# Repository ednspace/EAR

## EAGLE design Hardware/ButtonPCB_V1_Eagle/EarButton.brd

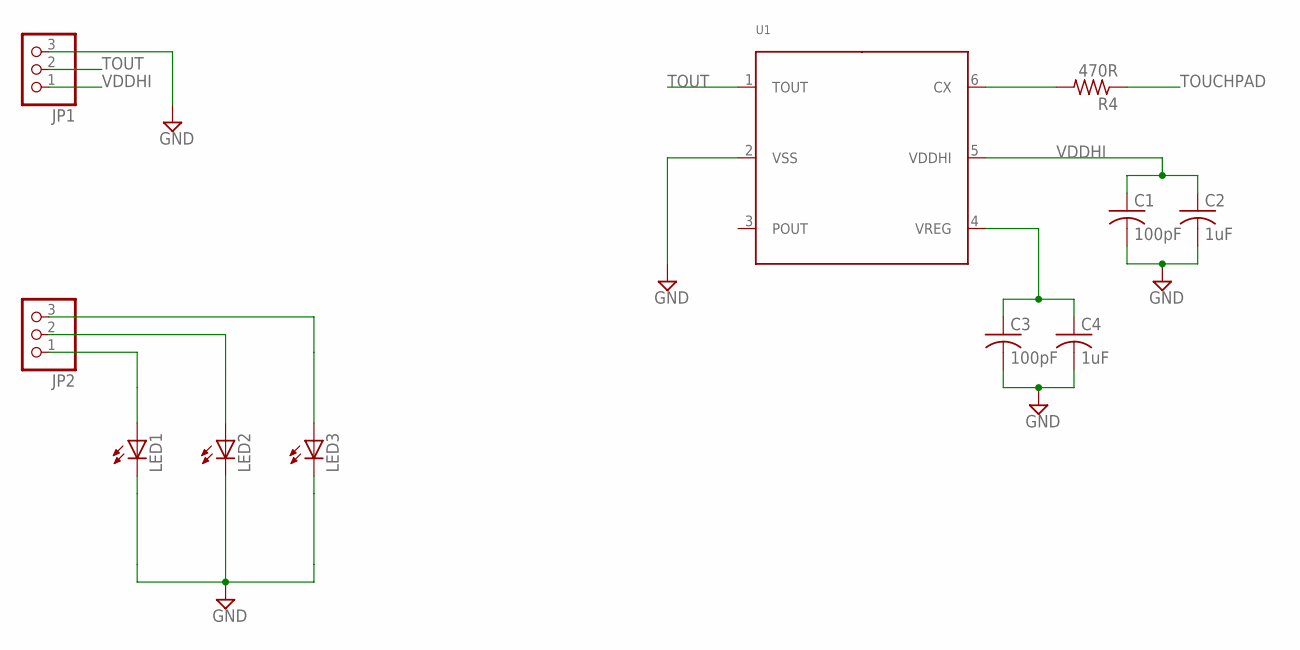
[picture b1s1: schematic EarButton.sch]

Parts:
C1, C3: 100pF; C0603K
C2, C4: 1uF; C0603K
JP1, JP2: PINHD-1X3; 1X03
LED1, LED2, LED3: LEDCHIPLED_1206; CHIPLED_1206
R4: 470R; R0603
U1: IQS127; SOT23-6

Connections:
GND: C1.2, C2.2, C3.2, C4.2, JP1.3, LED1.C, LED2.C, LED3.C, U1.2 (VSS)
unnamed: C3.1, C4.1, U1.4 (VREG)
unnamed: JP2.1, LED1.A
unnamed: JP2.2, LED2.A
unnamed: JP2.3, LED3.A
unnamed: R4.2, U1.6 (CX)
TOUCHPAD: R4.1
TOUT: JP1.2, U1.1 (TOUT)
VDDHI: C1.1, C2.1, JP1.1, U1.5 (VDDHI)

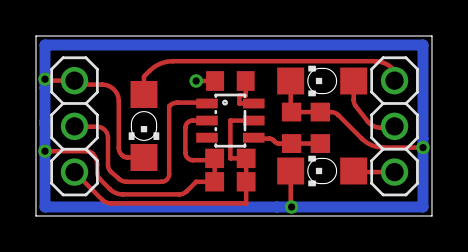
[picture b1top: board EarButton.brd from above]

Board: 2 copper layers, 22.0 x 10.0 mm, 11 parts (0 on the bottom side), 8 nets.

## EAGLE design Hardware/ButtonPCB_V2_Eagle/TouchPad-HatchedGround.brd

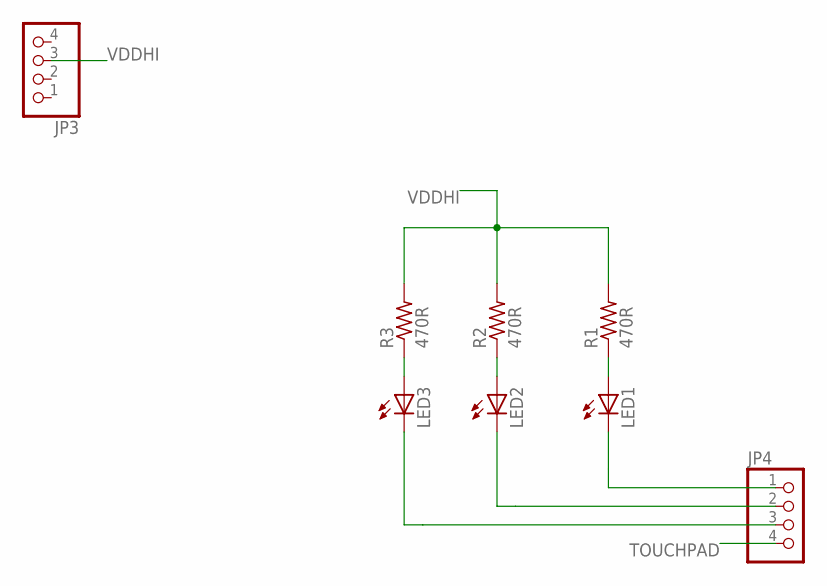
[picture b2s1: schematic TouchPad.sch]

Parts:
JP3, JP4: PINHD-1X4; 1X04
LED1, LED2, LED3: LEDCHIPLED_1206; CHIPLED_1206
R1, R2, R3: 470R; R0603

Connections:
GND: JP3.4
unnamed: LED1.A, R1.1
unnamed: LED2.A, R2.1
unnamed: LED3.A, R3.1
unnamed: JP4.1, LED1.C
unnamed: JP4.2, LED2.C
unnamed: JP4.3, LED3.C
TOUCHPAD: JP4.4
VDDHI: JP3.3, R1.2, R2.2, R3.2

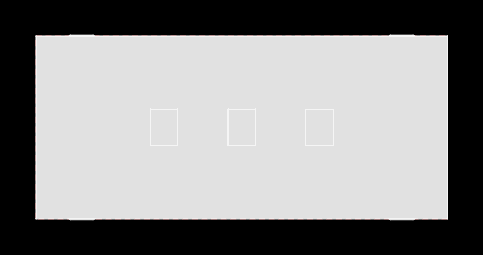
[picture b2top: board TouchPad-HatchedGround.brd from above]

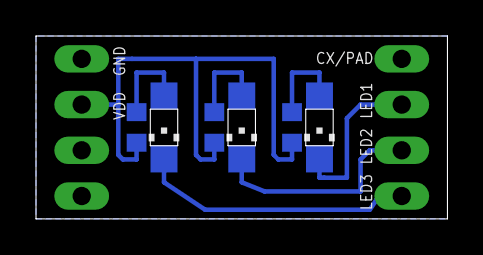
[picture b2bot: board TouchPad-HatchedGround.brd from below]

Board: 2 copper layers, 22.9 x 10.2 mm, 8 parts (6 on the bottom side), 7 nets.

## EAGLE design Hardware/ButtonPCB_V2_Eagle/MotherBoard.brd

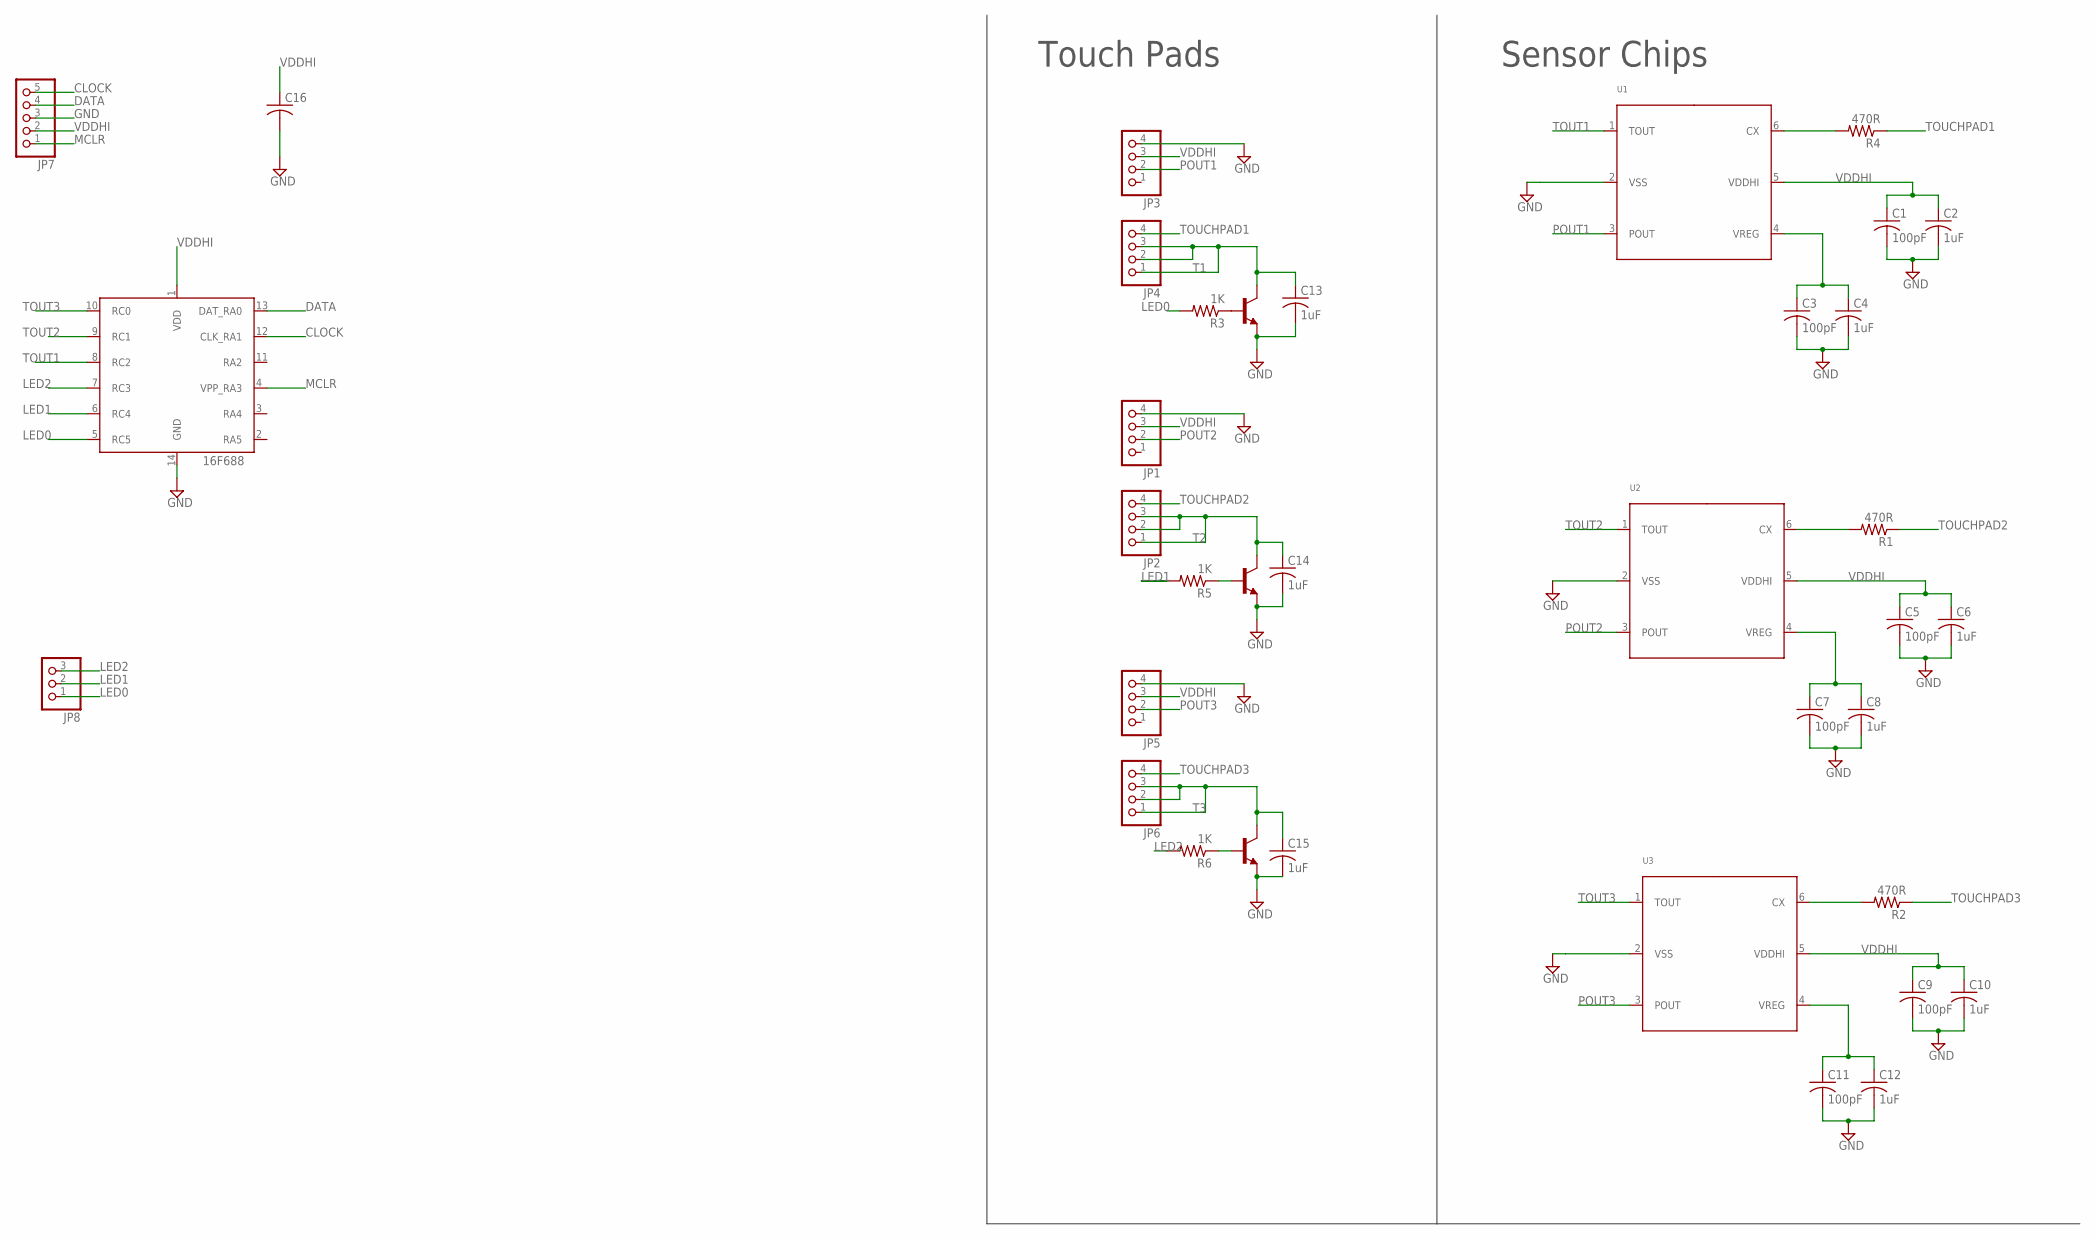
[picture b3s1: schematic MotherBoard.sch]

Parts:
C1, C3, C5, C7, C9, C11: 100pF; C0603K
C2, C4, C6, C8, C10, C12, C13, C14, C15: 1uF; C0603K
C16: C-USC1206; C1206
JP1, JP2, JP3, JP4, JP5, JP6: PINHD-1X4; 1X04
JP7: PINHD-1X5; 1X05
JP8: PINHD-1X3; 1X03
R1, R2, R4: 470R; R0603
R3, R5, R6: 1K; R0603
T1, T2, T3: BC818-NPN-SOT23-BEC; SOT23-BEC
U1, U2, U3: IQS127; SOT23-6
U$1: PIC16F688SOIC14; SOIC14

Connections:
CLOCK: JP7.5, U$1.12 (CLK_RA1)
DATA: JP7.4, U$1.13 (DAT_RA0)
GND: C1.2, C2.2, C3.2, C4.2, C5.2, C6.2, C7.2, C8.2, C9.2, C10.2, C11.2, C12.2, C13.2, C14.2, C15.2, C16.2, JP1.4, JP3.4, JP5.4, JP7.3, T1.E, T2.E, T3.E, U1.2 (VSS), U2.2 (VSS), U3.2 (VSS), U$1.14 (GND)
LED0: JP8.1, R3.2, U$1.5 (RC5)
LED1: JP8.2, R5.2, U$1.6 (RC4)
LED2: JP8.3, R6.2, U$1.7 (RC3)
MCLR: JP7.1, U$1.4 (VPP_RA3)
unnamed: C7.1, C8.1, U2.4 (VREG)
unnamed: R1.2, U2.6 (CX)
unnamed: C3.1, C4.1, U1.4 (VREG)
unnamed: C13.1, JP4.1, JP4.2, JP4.3, T1.C
unnamed: C14.1, JP2.1, JP2.2, JP2.3, T2.C
unnamed: C15.1, JP6.1, JP6.2, JP6.3, T3.C
unnamed: C11.1, C12.1, U3.4 (VREG)
unnamed: R4.2, U1.6 (CX)
unnamed: R3.1, T1.B
unnamed: R5.1, T2.B
unnamed: R6.1, T3.B
unnamed: R2.2, U3.6 (CX)
POUT1: JP3.2, U1.3 (POUT)
POUT2: JP1.2, U2.3 (POUT)
POUT3: JP5.2, U3.3 (POUT)
TOUCHPAD1: JP4.4, R4.1
TOUCHPAD2: JP2.4, R1.1
TOUCHPAD3: JP6.4, R2.1
TOUT1: U1.1 (TOUT), U$1.8 (RC2)
TOUT2: U2.1 (TOUT), U$1.9 (RC1)
TOUT3: U3.1 (TOUT), U$1.10 (RC0)
VDDHI: C1.1, C2.1, C5.1, C6.1, C9.1, C10.1, C16.1, JP1.3, JP3.3, JP5.3, JP7.2, U1.5 (VDDHI), U2.5 (VDDHI), U3.5 (VDDHI), U$1.1 (VDD)

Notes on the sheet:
Touch Pads
Sensor Chips

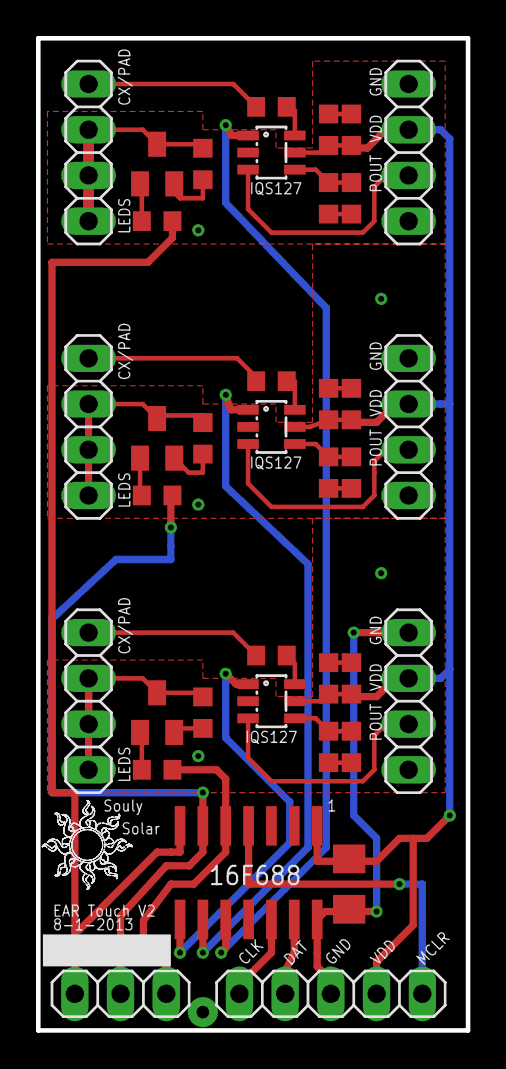
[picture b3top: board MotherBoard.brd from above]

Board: 2 copper layers, 23.9 x 55.1 mm, 38 parts (0 on the bottom side), 29 nets.

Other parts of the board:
U$2: SOULY-LOGO

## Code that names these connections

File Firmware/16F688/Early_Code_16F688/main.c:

#include <16F688.h>
//#device adc=10
#use delay(clock=8000000)
#fuses NOWDT,INTRC_IO, NOPROTECT, BROWNOUT, NOMCLR, NOCPD, PUT, NOIESO, NOFCMEN
//#use rs232(baud=9600,parity=N,xmit=PIN_C4,rcv=PIN_C5,bits=9)

#define LED0 PIN_C5
#define LED1 PIN_C4
#define LED2 PIN_C3

#define button0 PIN_C2
#define button1 PIN_C1
#define button2 PIN_C0

int1 state0,state1,state2;


void main(){
   setup_oscillator( OSC_8MHZ );
   //setup_adc_ports(sAN6|VSS_VDD);
   setup_adc(ADC_CLOCK_INTERNAL);
   //setup_counters(RTCC_INTERNAL,RTCC_DIV_1);
   //setup_timer_1(T1_DISABLED);
   setup_comparator(NC_NC_NC_NC);
   setup_vref(FALSE);

state0 = read_eeprom (0);
state1 = read_eeprom (1);
state2 = read_eeprom (2);

//Test the LEDs
/*
while (1){
output_low(LED0);
output_low(LED1);
output_low(LED2);
delay_ms(1000);
output_high(LED0);
output_high(LED1);
output_high(LED2);
delay_ms(1000);
}
*/

//The LEDs are an active High because of the NPN transistor driving the low side
if (state0 == 1)
output_high(LED0);

if (state1 == 1)
output_high(LED1);

if (state2 == 1)
output_high(LED2);

//The buttons are an active high to avoid problems with powerdown causing false triggers
//
   while(true)
   {
   
      if(input(button0)){
         //Toggle the LED
         output_toggle(LED0);
         while (input(button0)){} //Stay right here until button is released
         //We know button was pressed and released
         state0 = !state0;
         write_eeprom(0, state0);
        
      }
   
      if(input(button1)){
         //Toggle the LED
         output_toggle(LED1);
         while (input(button1)){} //Stay right here until button is released
         //We know button was pressed and released
         state1 = !state1;
         write_eeprom(1, state1);
         
      }
      
      if( input(button2) ){
         output_toggle(LED2);
         while (input(button2)){} //Stay right here until button is released
         //We know button was pressed and released
         state2 = !state2;
         write_eeprom(2, state2);
         
         
      }
   }

}

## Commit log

2014-11-06 Drawing the TapTempo schematic adding the first of the components
2014-11-07 Added the DAC and cleaned up the schematic a little bit.
2014-11-12 Anotation of schematic plus initial parts selection
2014-11-13 still organizing
2015-02-12 Added LUT table to firmware for VCO also added spreadsheet for LUT
2015-06-20 Lots of changes to the TapTempo Board, made it all consistantly surface mount, turned into a module and created gerbers.
2015-09-22 Pushing latest schematic brd file and some 12F1822 tests
2015-09-22 Pushing all updates mostly code tests and some TT board changes
2015-10-08 Updating codebase with delivered code that is AWESOME and TEENSYLC test code plus new spreadsheets for error calculation...
2016-07-22 Updating TapTempo.pro
